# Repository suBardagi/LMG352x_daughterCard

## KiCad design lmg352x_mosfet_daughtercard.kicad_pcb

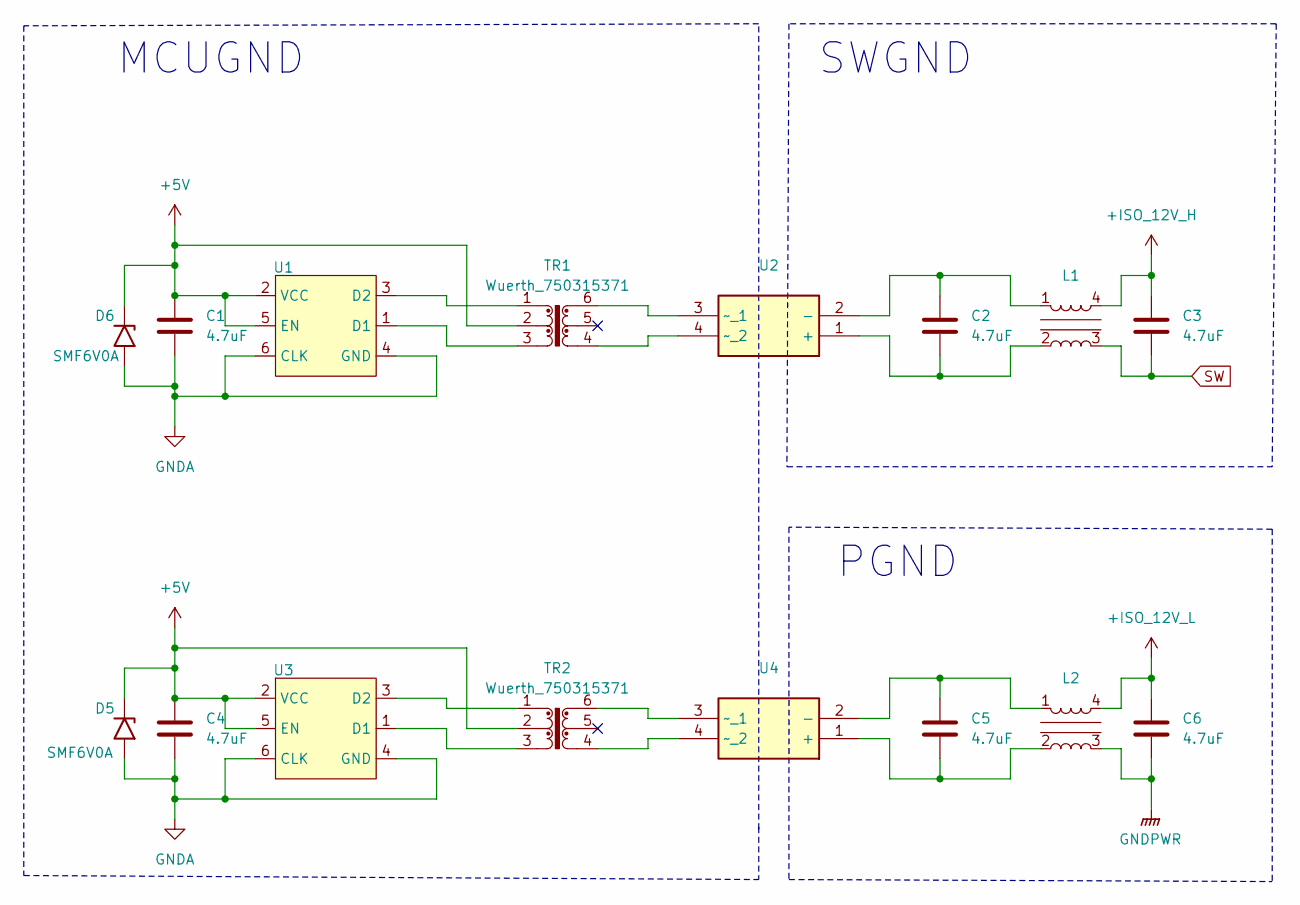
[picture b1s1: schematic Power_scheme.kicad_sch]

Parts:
C1, C2, C3, C4, C5, C6: 4.7uF; C_0805_2012Metric_Pad1.18x1.45mm_HandSolder
D5, D6: SMF6V0A; D_SMF
L1, L2: ACM2012-900-2P-T001
TR1, TR2: Wuerth_750315371; 750315371
U1, U3: SN6505B
U2, U4: TS260S_R2_00001

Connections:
+5V: C1.1, C4.1, D5.1 (A1), D6.1 (A1), TR1.2, TR2.2, U1.2 (VCC), U1.5 (EN), U3.2 (VCC), U3.5 (EN); also elsewhere on the board
+ISO_12V_H: C3.1, L1.4; also elsewhere on the board
+ISO_12V_L: C6.1, L2.4; also elsewhere on the board
GNDA: C1.2, C4.2, D5.2 (A2), D6.2 (A2), U1.4 (GND), U1.6 (CLK), U3.4 (GND), U3.6 (CLK); also elsewhere on the board
GNDPWR: C6.2, L2.3; also elsewhere on the board
unnamed: TR1.3, U1.1 (D1)
unnamed: TR1.1, U1.3 (D2)
unnamed: C2.2, L1.2, U2.1 (+)
unnamed: C2.1, L1.1, U2.2 (-)
unnamed: TR1.6, U2.3 (~_1)
unnamed: TR1.4, U2.4 (~_2)
unnamed: TR2.3, U3.1 (D1)
unnamed: TR2.1, U3.3 (D2)
unnamed: C5.2, L2.2, U4.1 (+)
unnamed: C5.1, L2.1, U4.2 (-)
unnamed: TR2.6, U4.3 (~_1)
unnamed: TR2.4, U4.4 (~_2)
SW: C3.2, L1.3; also elsewhere on the board

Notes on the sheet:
MCUGND
SWGND
PGND

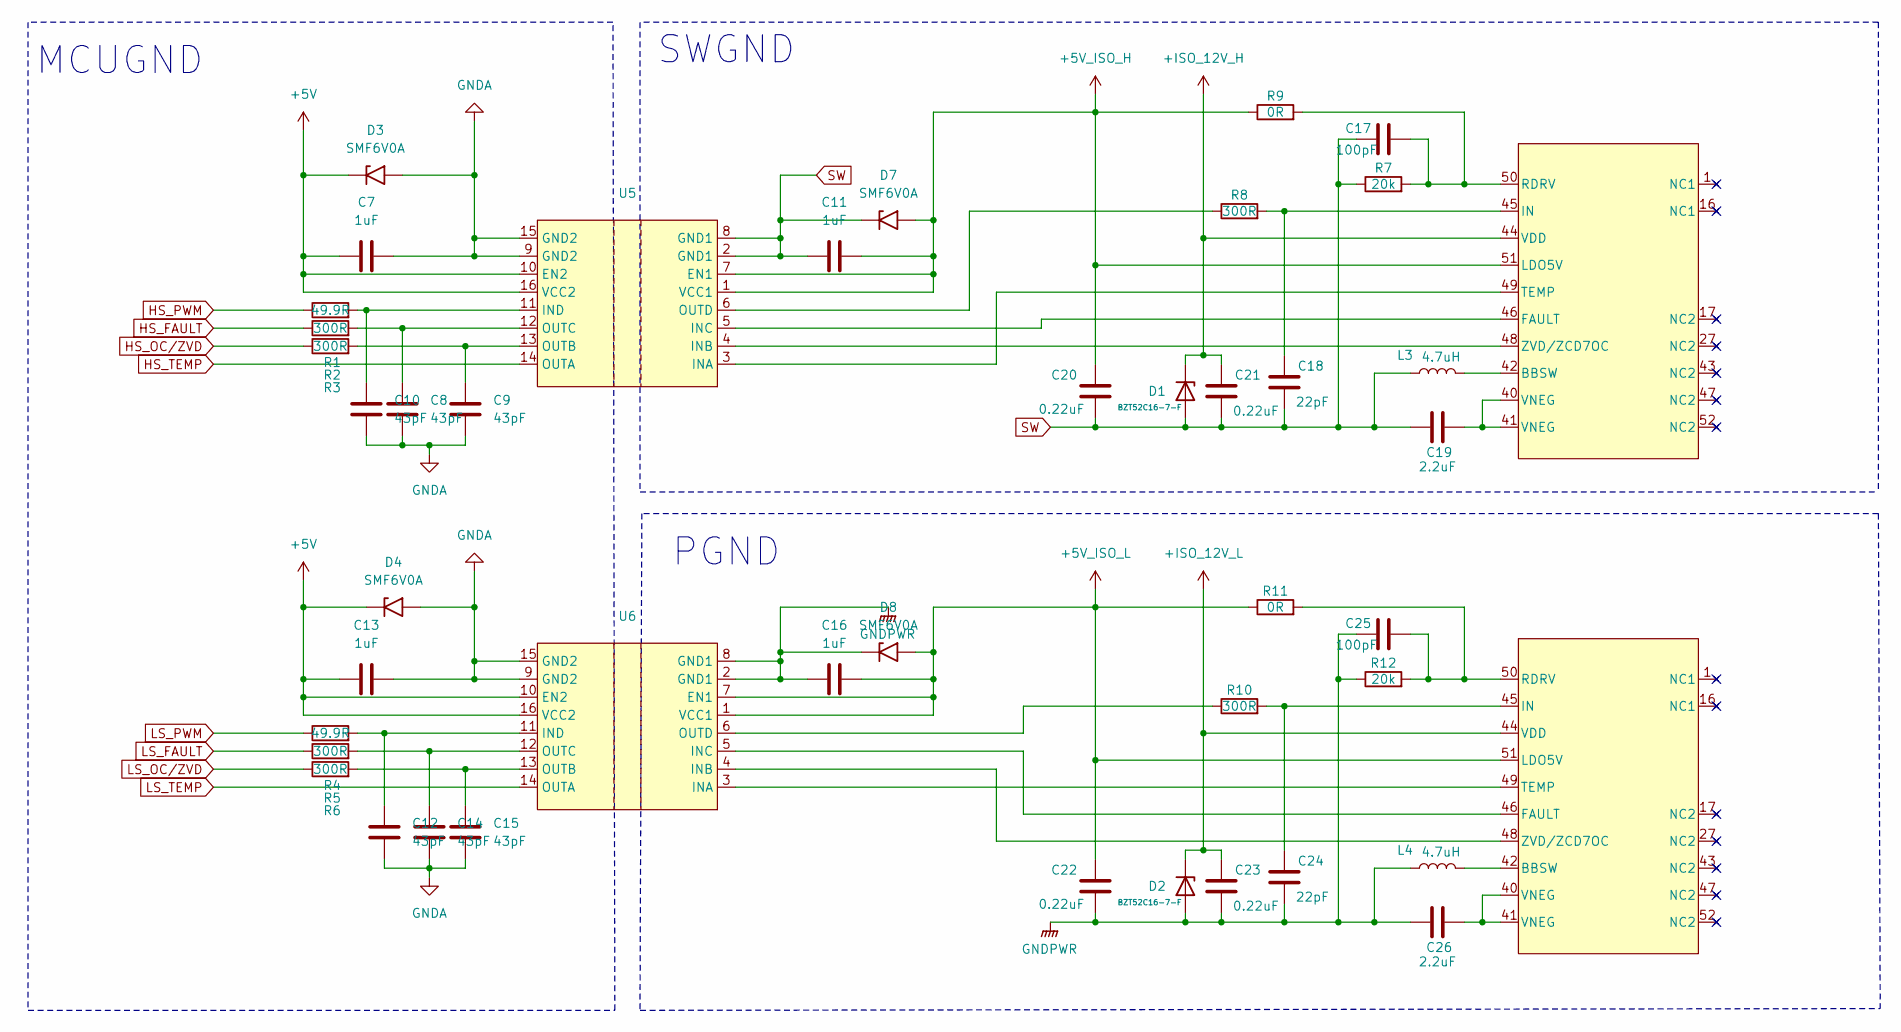
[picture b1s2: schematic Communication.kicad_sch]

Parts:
C7, C11, C13, C16: 1uF; C_0805_2012Metric_Pad1.18x1.45mm_HandSolder
C8, C9, C10, C12, C14, C15: 43pF; C_0805_2012Metric_Pad1.18x1.45mm_HandSolder
C17, C25: 100pF; C_0805_2012Metric_Pad1.18x1.45mm_HandSolder
C18, C24: 22pF; C_0805_2012Metric_Pad1.18x1.45mm_HandSolder
C19, C26: 2.2uF; C_0805_2012Metric_Pad1.18x1.45mm_HandSolder
C20, C21, C22, C23: 0.22uF; C_0805_2012Metric_Pad1.18x1.45mm_HandSolder
D1, D2: BZT52C16-7-F; D_SOD-123F
D3, D4, D7, D8: SMF6V0A; D_SMF
L3, L4: 4.7uH; Ind_6.3mmx6.3mm
R1, R4: 49.9R; R_0805_2012Metric_Pad1.20x1.40mm_HandSolder
R2, R3, R5, R6, R8, R10: 300R; R_0805_2012Metric_Pad1.20x1.40mm_HandSolder
R7, R12: 20k; R_0805_2012Metric_Pad1.20x1.40mm_HandSolder
R9, R11: 0R; R_0805_2012Metric_Pad1.20x1.40mm_HandSolder
U5, U6: DW0016B_HV
U7, U8: LMG352x

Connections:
+5V: C7.1, C13.1, D3.1 (A1), D4.1 (A1), U5.10 (EN2), U5.16 (VCC2), U6.10 (EN2), U6.16 (VCC2); also elsewhere on the board
+5V_ISO_H: C11.2, C20.1, D7.2 (A2), R9.1, U5.1 (VCC1), U5.7 (EN1), U7.51 (LDO5V)
+5V_ISO_L: C16.2, C22.1, D8.2 (A2), R11.1, U6.1 (VCC1), U6.7 (EN1), U8.51 (LDO5V)
+ISO_12V_H: C21.1, D1.1 (K), U7.44 (VDD); also elsewhere on the board
+ISO_12V_L: C23.1, D2.1 (K), U8.44 (VDD); also elsewhere on the board
GNDA: C7.2, C8.1, C9.1, C10.1, C12.1, C13.2, C14.1, C15.1, D3.2 (A2), D4.2 (A2), U5.9 (GND2), U5.15 (GND2), U6.9 (GND2), U6.15 (GND2); also elsewhere on the board
GNDPWR: C16.1, C22.2, C23.2, C24.2, C25.1, C26.1, D2.2 (A), D8.1 (A1), L4.1, R12.1, U6.2 (GND1), U6.8 (GND1); also elsewhere on the board
HS_FAULT: R2.1
HS_OC/ZVD: R3.1
HS_PWM: R1.1
HS_TEMP: U5.14 (OUTA)
LS_FAULT: R5.1
LS_OC/ZVD: R6.1
LS_PWM: R4.1
LS_TEMP: U6.14 (OUTA)
unnamed: C19.2, U7.40 (VNEG), U7.41 (VNEG)
unnamed: C26.2, U8.40 (VNEG), U8.41 (VNEG)
unnamed: U5.3 (INA), U7.49 (TEMP)
unnamed: U5.4 (INB), U7.48 (ZVD/ZCD7OC)
unnamed: U5.5 (INC), U7.46 (FAULT)
unnamed: C10.2, R1.2, U5.11 (IND)
unnamed: C9.2, R3.2, U5.13 (OUTB)
unnamed: C8.2, R2.2, U5.12 (OUTC)
unnamed: R8.1, U5.6 (OUTD)
unnamed: U6.3 (INA), U8.49 (TEMP)
unnamed: U6.4 (INB), U8.48 (ZVD/ZCD7OC)
unnamed: U6.5 (INC), U8.46 (FAULT)
unnamed: C12.2, R4.2, U6.11 (IND)
unnamed: C15.2, R6.2, U6.13 (OUTB)
unnamed: C14.2, R5.2, U6.12 (OUTC)
unnamed: R10.1, U6.6 (OUTD)
unnamed: L3.2, U7.42 (BBSW)
unnamed: C18.1, R8.2, U7.45 (IN)
unnamed: C17.2, R7.2, R9.2, U7.50 (RDRV)
unnamed: L4.2, U8.42 (BBSW)
unnamed: C24.1, R10.2, U8.45 (IN)
unnamed: C25.2, R11.2, R12.2, U8.50 (RDRV)
SW: C11.1, C17.1, C18.2, C19.1, C20.2, C21.2, D1.2 (A), D7.1 (A1), L3.1, R7.1, U5.2 (GND1), U5.8 (GND1); also elsewhere on the board

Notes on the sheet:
PGND
SWGND
MCUGND

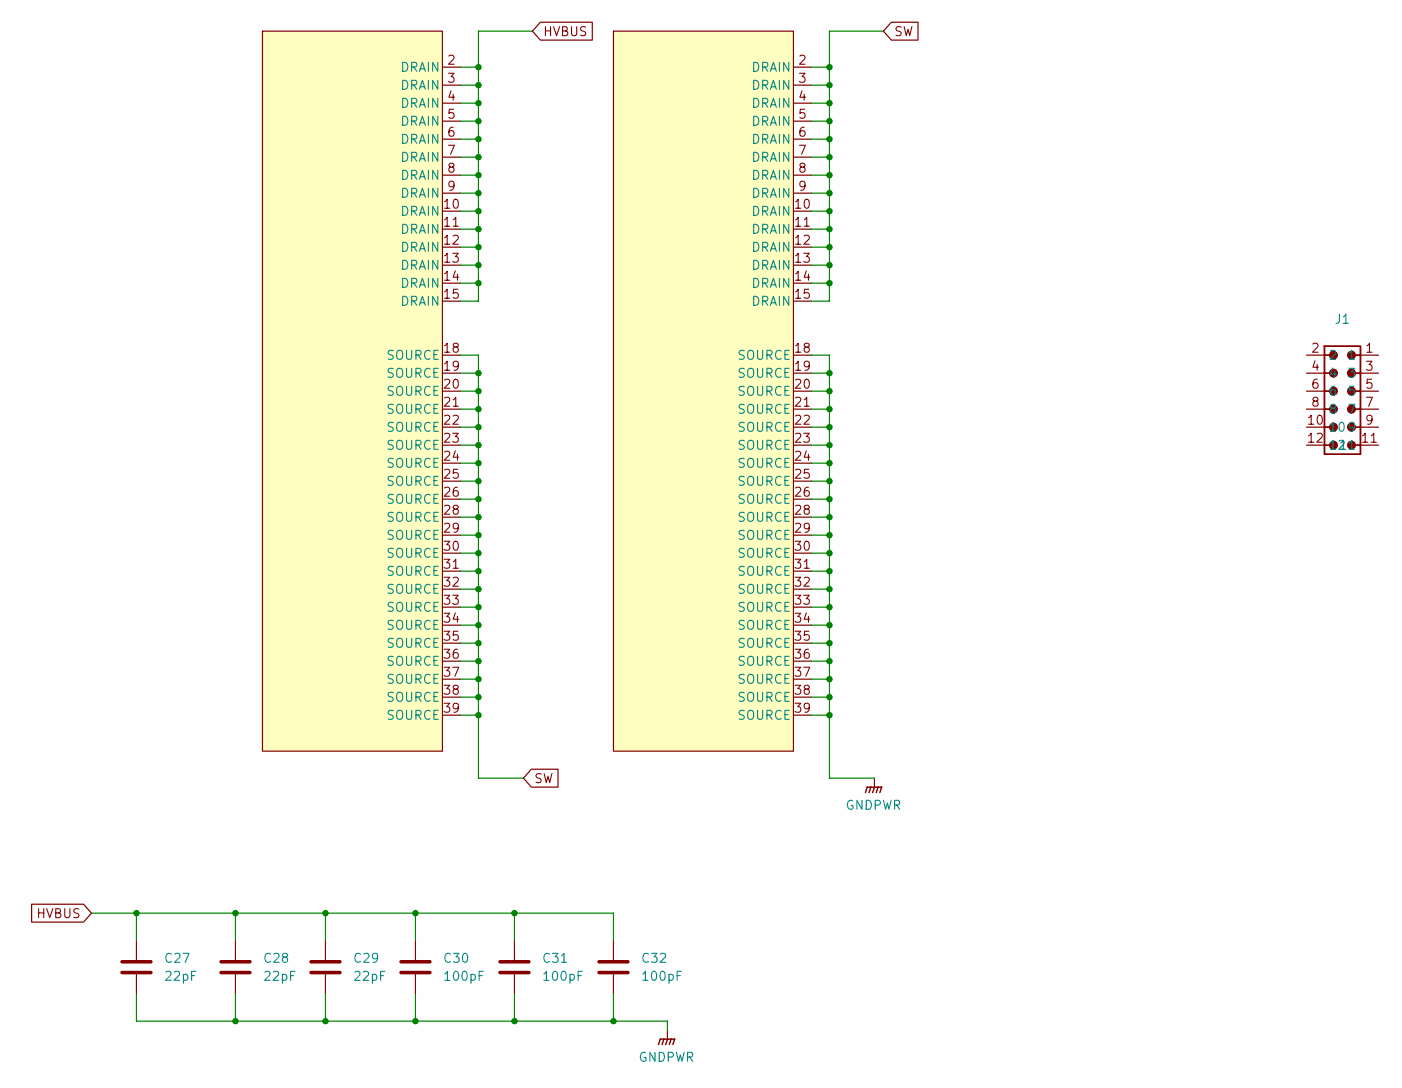
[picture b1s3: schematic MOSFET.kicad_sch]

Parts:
C27, C28, C29: 22pF; C_1210_3225Metric_Pad1.33x2.70mm_HandSolder
C30, C31, C32: 100pF; C_1206_3216Metric_Pad1.33x1.80mm_HandSolder
J1: PinHeader_2x6_Angled
U7, U8: LMG352x

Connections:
GNDPWR: C27.2, C28.2, C29.2, C30.2, C31.2, C32.2, U8.18 (SOURCE), U8.19 (SOURCE), U8.20 (SOURCE), U8.21 (SOURCE), U8.22 (SOURCE), U8.23 (SOURCE), U8.24 (SOURCE), U8.25 (SOURCE), U8.26 (SOURCE), U8.28 (SOURCE), U8.29 (SOURCE), U8.30 (SOURCE), U8.31 (SOURCE), U8.32 (SOURCE), U8.33 (SOURCE), U8.34 (SOURCE), U8.35 (SOURCE), U8.36 (SOURCE), U8.37 (SOURCE), U8.38 (SOURCE), U8.39 (SOURCE); also elsewhere on the board
HVBUS: C27.1, C28.1, C29.1, C30.1, C31.1, C32.1, U7.2 (DRAIN), U7.3 (DRAIN), U7.4 (DRAIN), U7.5 (DRAIN), U7.6 (DRAIN), U7.7 (DRAIN), U7.8 (DRAIN), U7.9 (DRAIN), U7.10 (DRAIN), U7.11 (DRAIN), U7.12 (DRAIN), U7.13 (DRAIN), U7.14 (DRAIN), U7.15 (DRAIN)
SW: U7.18 (SOURCE), U7.19 (SOURCE), U7.20 (SOURCE), U7.21 (SOURCE), U7.22 (SOURCE), U7.23 (SOURCE), U7.24 (SOURCE), U7.25 (SOURCE), U7.26 (SOURCE), U7.28 (SOURCE), U7.29 (SOURCE), U7.30 (SOURCE), U7.31 (SOURCE), U7.32 (SOURCE), U7.33 (SOURCE), U7.34 (SOURCE), U7.35 (SOURCE), U7.36 (SOURCE), U7.37 (SOURCE), U7.38 (SOURCE), U7.39 (SOURCE), U8.2 (DRAIN), U8.3 (DRAIN), U8.4 (DRAIN), U8.5 (DRAIN), U8.6 (DRAIN), U8.7 (DRAIN), U8.8 (DRAIN), U8.9 (DRAIN), U8.10 (DRAIN), U8.11 (DRAIN), U8.12 (DRAIN), U8.13 (DRAIN), U8.14 (DRAIN), U8.15 (DRAIN); also elsewhere on the board

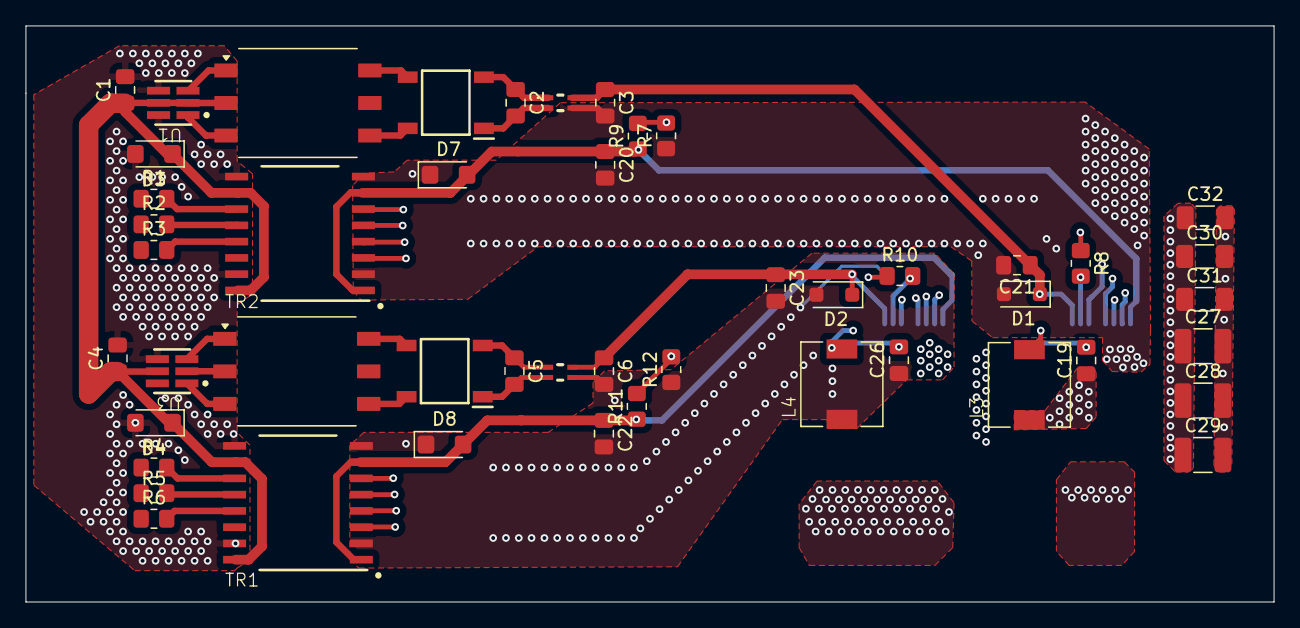
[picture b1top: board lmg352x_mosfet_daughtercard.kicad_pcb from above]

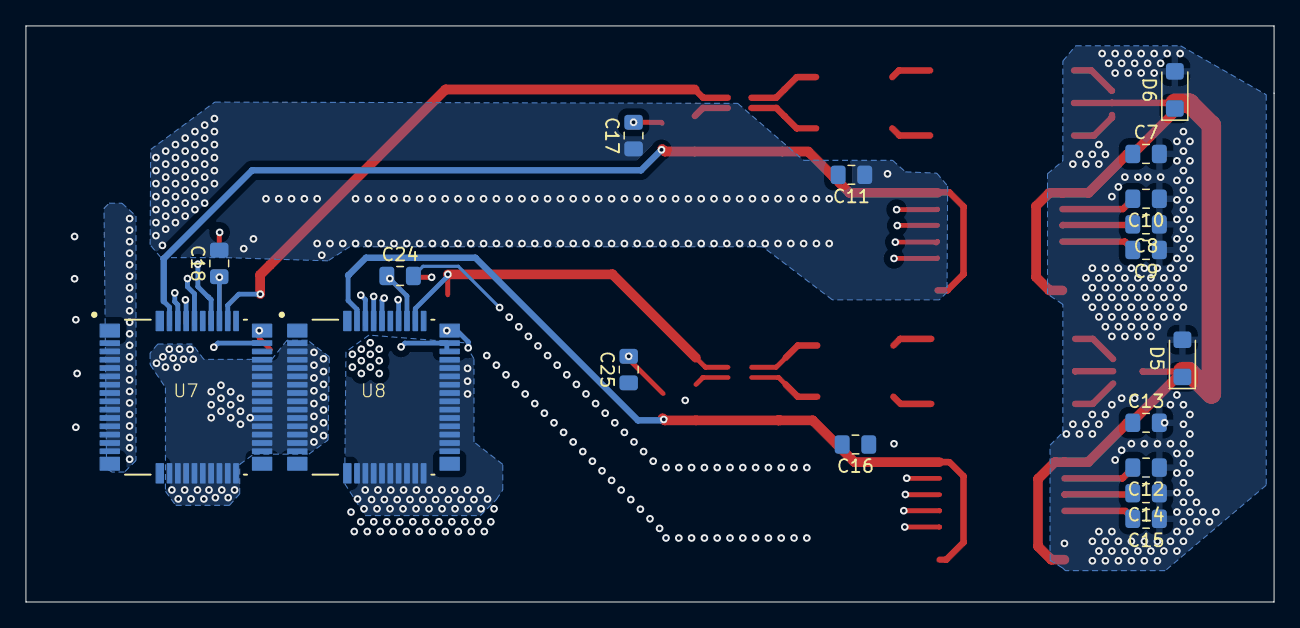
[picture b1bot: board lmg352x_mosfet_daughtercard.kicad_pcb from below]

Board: 4 copper layers, 97.5 x 45.0 mm, 66 parts (18 on the bottom side), 43 nets.

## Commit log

2025-09-02 Documents_v1
2025-09-02 Changes(02092025)
2025-09-10 added vias
2025-09-13 added via for PGND
2025-09-15 little changes in 15.9.2025
